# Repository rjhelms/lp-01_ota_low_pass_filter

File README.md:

# LP-01 OTA Low Pass Filter
[![CC BY-SA 4.0][cc-by-sa-shield]][cc-by-sa]

A Eurorack low-pass filter, in the style of the classic MS-20 circuit, featuring two CV inputs - one adjustable, the other with roughly 1V/oct tracking.

* Width: 8hp
* Depth: 23mm

This project was created with [KiCad](https://kicad.org/).

This work licensed under a
[Creative Commons Attribution-ShareAlike 4.0 International License][cc-by-sa].

[![CC BY-SA 4.0][cc-by-sa-image]][cc-by-sa]

[cc-by-sa]: http://creativecommons.org/licenses/by-sa/4.0/
[cc-by-sa-image]: https://licensebuttons.net/l/by-sa/4.0/88x31.png
[cc-by-sa-shield]: https://img.shields.io/badge/License-CC%20BY--SA%204.0-lightgrey.svg

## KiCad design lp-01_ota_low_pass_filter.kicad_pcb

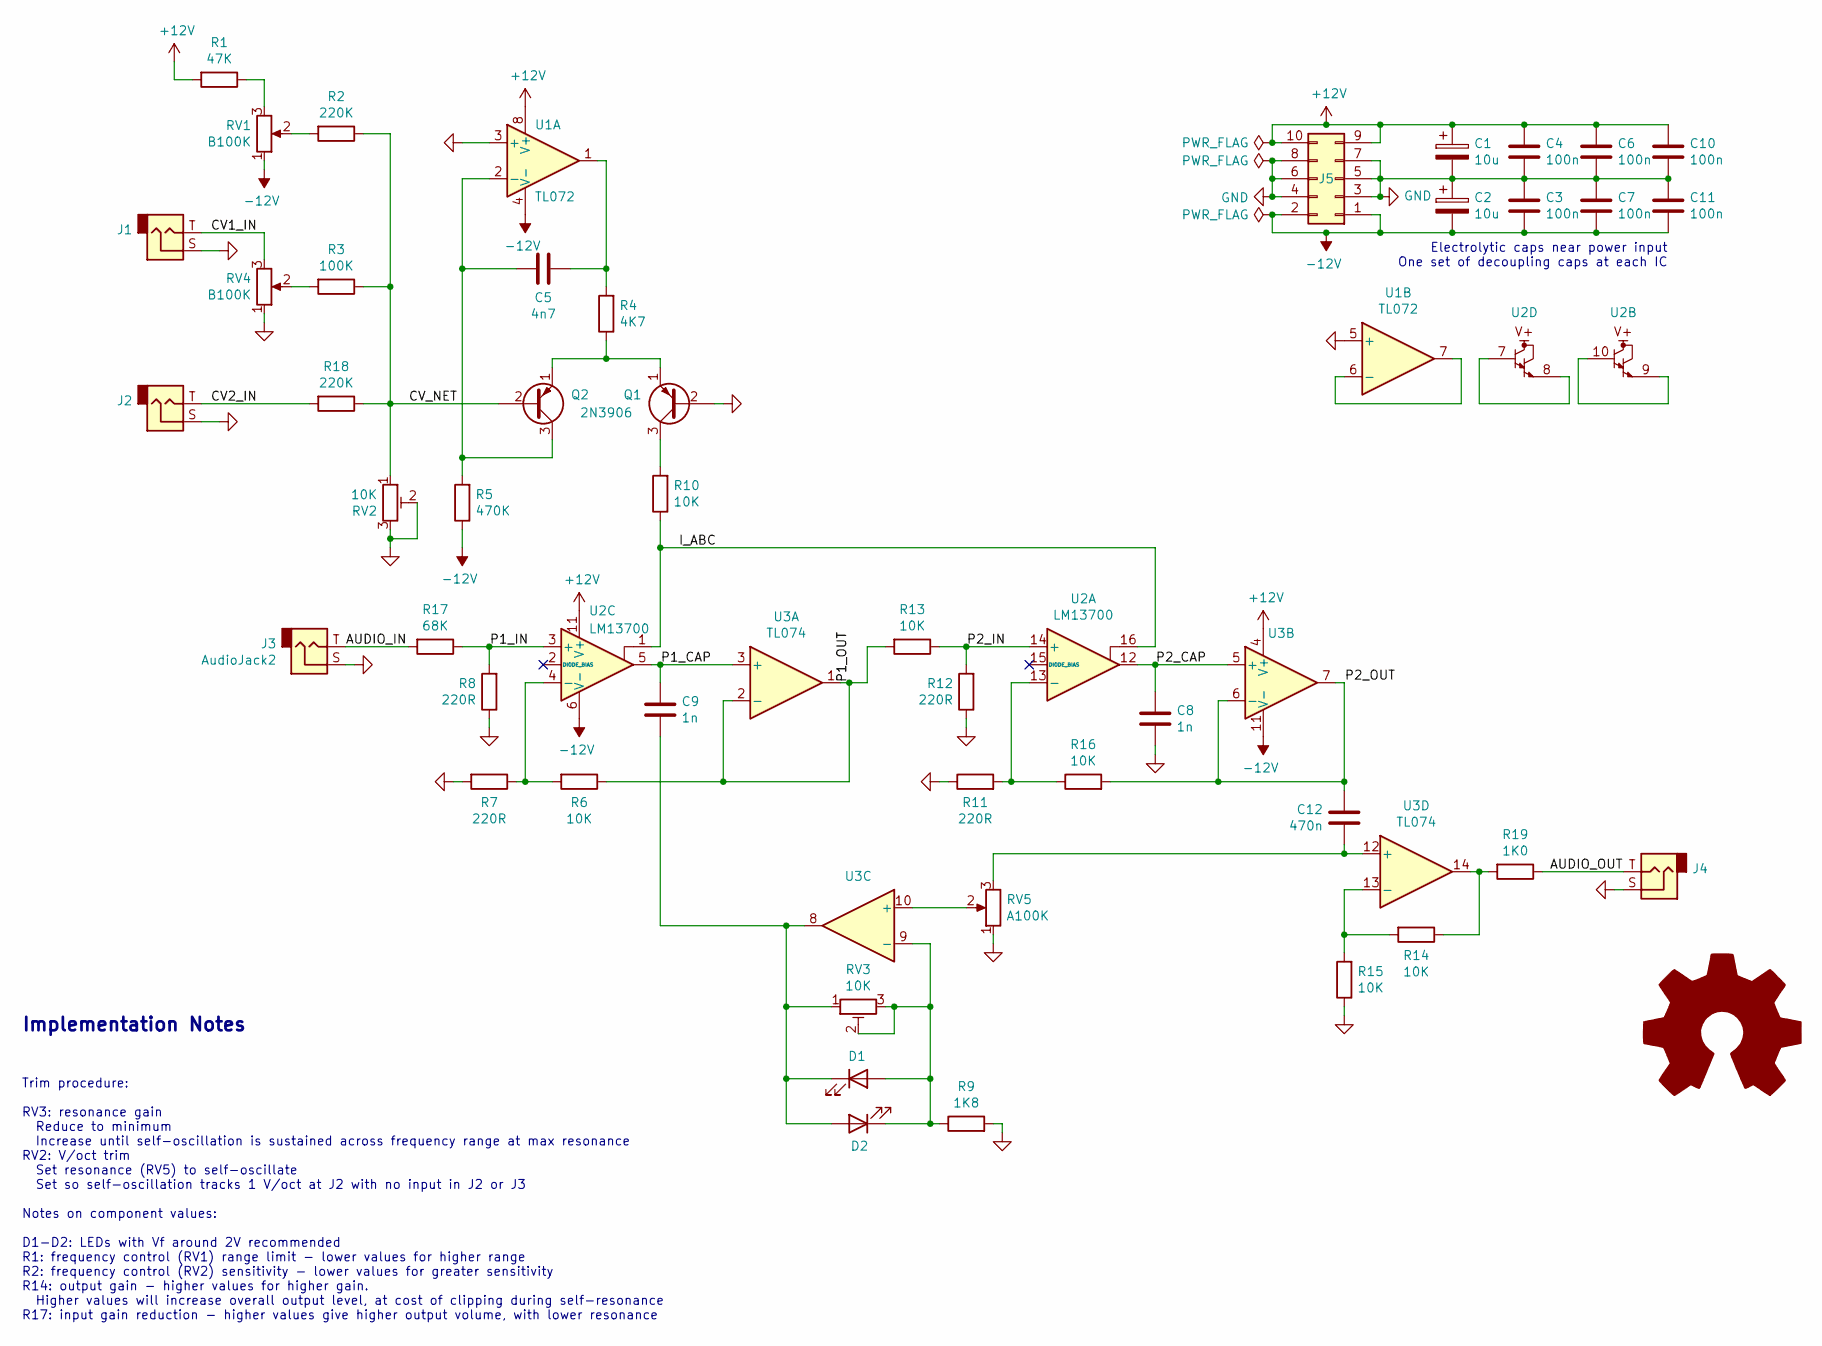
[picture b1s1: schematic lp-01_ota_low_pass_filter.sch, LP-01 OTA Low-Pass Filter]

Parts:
C1, C2: 10u; CP_Radial_D4.0mm_P1.50mm
C3, C4, C6, C7, C10, C11: 100n; C_Disc_D5.0mm_W2.5mm_P2.50mm
C5: 4n7; C_Disc_D5.0mm_W2.5mm_P2.50mm
C8, C9: 1n; C_Disc_D5.0mm_W2.5mm_P2.50mm
C12: 470n; C_Disc_D5.0mm_W2.5mm_P2.50mm
D1, D2: LED Green; LED_D5.0mm
J1, J2, J3, J4: AudioJack2; Jack_3.5mm_QingPu_WQP-PJ398SM_Vertical_CircularHoles
J5: Conn_02x05_Odd_Even; PinHeader_2x05_P2.54mm_Vertical
LOGO1: Logo_Open_Hardware_Large; OSHW-Logo_5.7x6mm_SilkScreen
Q1, Q2: 2N3906; TO-92_Inline_Wide
R1: 47K; R_Axial_DIN0204_L3.6mm_D1.6mm_P5.08mm_Horizontal
R2, R18: 220K; R_Axial_DIN0204_L3.6mm_D1.6mm_P5.08mm_Horizontal
R3: 100K; R_Axial_DIN0204_L3.6mm_D1.6mm_P5.08mm_Horizontal
R4: 4K7; R_Axial_DIN0204_L3.6mm_D1.6mm_P5.08mm_Horizontal
R5: 470K; R_Axial_DIN0204_L3.6mm_D1.6mm_P5.08mm_Horizontal
R6, R10, R13, R14, R15, R16: 10K; R_Axial_DIN0204_L3.6mm_D1.6mm_P5.08mm_Horizontal
R7, R8, R11, R12: 220R; R_Axial_DIN0204_L3.6mm_D1.6mm_P5.08mm_Horizontal
R9: 1K8; R_Axial_DIN0204_L3.6mm_D1.6mm_P5.08mm_Horizontal
R17: 68K; R_Axial_DIN0204_L3.6mm_D1.6mm_P5.08mm_Horizontal
R19: 1K0; R_Axial_DIN0204_L3.6mm_D1.6mm_P5.08mm_Horizontal
RV1, RV4: B100K; Potentiometer_Alpha_RD901F-40-00D_Single_Vertical
RV2, RV3: 10K; Potentiometer_Bourns_PV36W
RV5: A100K; Potentiometer_Alpha_RD901F-40-00D_Single_Vertical
U1: TL072; DIP-8_W7.62mm_Socket
U2: LM13700; DIP-16_W7.62mm_Socket
U3: TL074; DIP-14_W7.62mm_Socket

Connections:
+12V: C1.1, C4.1, C6.1, C10.1, J5.9, J5.10, R1.2, U1.8 (V+), U2.11 (V+), U3.4 (V+)
-12V: C2.2, C3.2, C7.2, C11.2, J5.1, J5.2, R5.1, RV1.1, U1.4 (V-), U2.6 (V-), U3.11 (V-)
/AUDIO_IN: J3.T, R17.2
/AUDIO_OUT: J4.T, R19.1
/CV1_IN: J1.T, RV4.3
/CV2_IN: J2.T, R18.2
/CV_NET: Q2.2 (B), R2.1, R3.1, R18.1, RV2.1
/I_ABC: R10.1, U2.1, U2.16
/P1_CAP: C9.1, U2.5, U3.3 (+)
/P1_IN: R8.2, R17.1, U2.3 (+)
/P1_OUT: R6.1, R13.2, U3.1, U3.2 (-)
/P2_CAP: C8.1, U2.12, U3.5 (+)
/P2_IN: R12.2, R13.1, U2.14 (+)
/P2_OUT: C12.2, R16.2, U3.6 (-), U3.7
GND: C1.2, C2.1, C3.1, C4.2, C6.2, C7.1, C8.2, C10.2, C11.1, J1.S, J2.S, J3.S, J4.S, J5.3, J5.4, J5.5, J5.6, J5.7, J5.8, Q1.2 (B), R7.2, R8.1, R9.2, R11.1, R12.1, R15.1, RV2.2, RV2.3, RV4.1, RV5.1, U1.3 (+), U1.5 (+)
unnamed: C5.1, R4.2, U1.1
unnamed: C5.2, Q2.3 (C), R5.2, U1.2 (-)
unnamed: C9.2, D1.1 (K), D2.2 (A), RV3.1, U3.8
unnamed: C12.1, RV5.3, U3.12 (+)
unnamed: D1.2 (A), D2.1 (K), R9.1, RV3.2, RV3.3, U3.9 (-)
unnamed: Q1.1 (E), Q2.1 (E), R4.1
unnamed: Q1.3 (C), R10.2
unnamed: R1.1, RV1.3
unnamed: R2.2, RV1.2
unnamed: R3.2, RV4.2
unnamed: R6.2, R7.1, U2.4 (-)
unnamed: R11.2, R16.1, U2.13 (-)
unnamed: R14.1, R19.2, U3.14
unnamed: R14.2, R15.2, U3.13 (-)
unnamed: RV5.2, U3.10 (+)
unnamed: U1.6 (-), U1.7
unnamed: U2.7, U2.8
unnamed: U2.9, U2.10

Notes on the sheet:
Electrolytic caps near power input One set of decoupling caps at each IC
Trim procedure: RV3: resonance gain Reduce to minimum Increase until self-oscillation is sustained across frequency range at max resonance RV2: V/oct trim Set resonance (RV5) to self-oscillate Set so self-oscillation tracks 1 V/oct at J2 with no input in J2 or J3 Notes on component values: D1-D2: L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
Implementation Notes

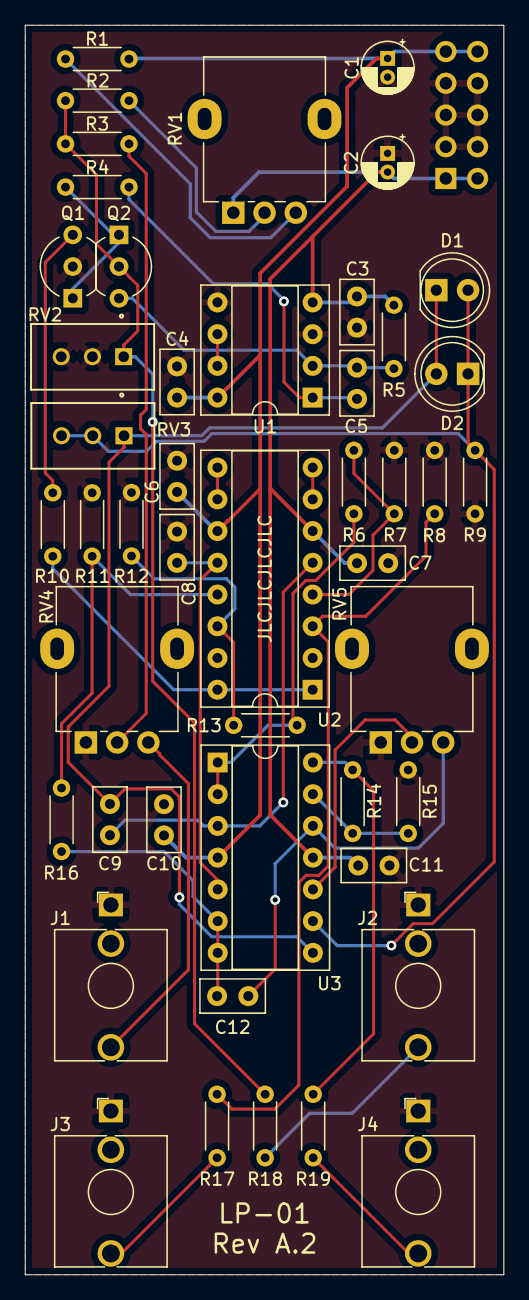
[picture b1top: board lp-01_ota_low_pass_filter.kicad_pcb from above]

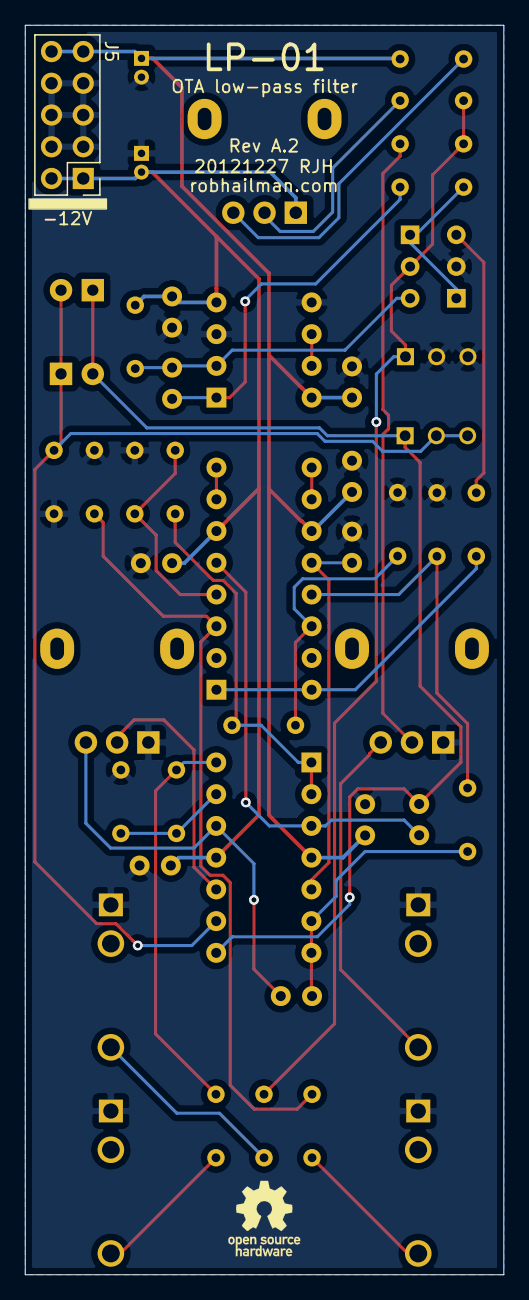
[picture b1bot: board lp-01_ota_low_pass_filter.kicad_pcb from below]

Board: 2 copper layers, 38.3 x 100.0 mm, 49 parts (2 on the bottom side), 33 nets.

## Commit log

2019-09-15 Initial commit
    Work to date - before fabbing RevA
2019-09-15 Correct RV2 set instructions
2019-09-18 Move back side text on panel
2019-09-18 Finalize settings for RevA export
2019-10-04 Add IC sockets to BOM
2020-01-18 Rev A1 - revised component values
    Increase CV1 input impedance, and adjust values for V/oct at CV2
2020-12-27 Assign license
2020-12-27 Revision A.2
    - A few small component tweaks
    - Add OSHW logos
    - Prepare for public release?
2020-12-29 Revert RV5 to log pot
    This works much better!
2020-12-29 Update PDF schematic
2020-12-29 Update CSV BOM

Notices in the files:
lp-01_ota_low_pass_filter.kicad_pcb:
Attribution-ShareAlike 4.0 International (CC BY-SA 4.0)
parts and their libraries:
Copyright 2016 Accelerated Designs. All rights reserved.
